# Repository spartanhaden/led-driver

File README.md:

# LED driver

This repo contains code for a [Particle Photon](https://docs.particle.io/quickstart/photon/) used to control a strip of 12V RGB LEDs connected to a custom designed a PCB. The brd and sch files are also included.

## Schematic

## Board

## Breadboard

## PCB

## Assembled PCB

## Assembled unit

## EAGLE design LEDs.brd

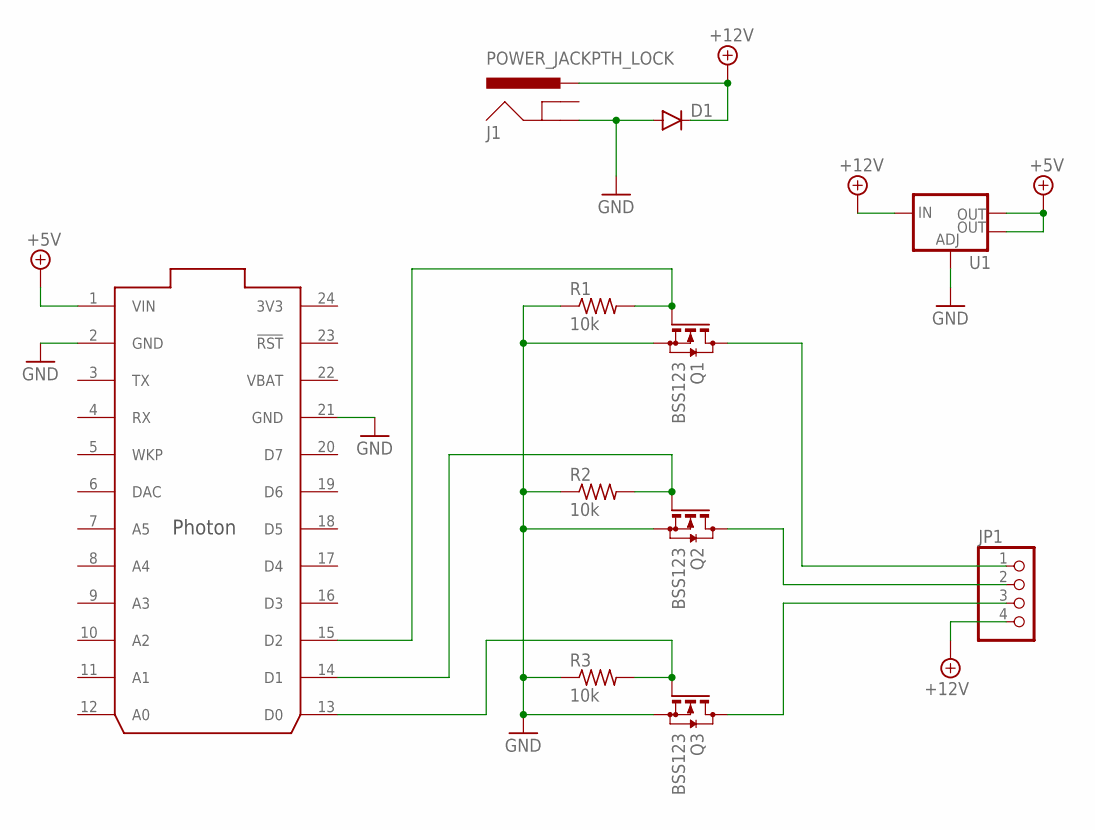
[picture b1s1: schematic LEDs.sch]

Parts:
D1: DIODESMA; SMA-DIODE
J1: POWER_JACKPTH_LOCK; POWER_JACK_PTH_LOCK
JP1: PINHD-1X4/90; 1X04/90
Q1, Q2, Q3: BSS123; SOT23
R1, R2, R3: 10k; M0805
U1: V_REG_LM1117SOT223; SOT223
U$1: PHOTON_WITH_HEADERS; PHOTON

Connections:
3V3: U$1.24 (3V3)
+5V: U1.2 (OUT), U1.4 (OUT), U$1.1 (VIN)
+12V: D1.C, J1.PWR, JP1.4, U1.3 (IN)
GND: D1.A, J1.GND, Q1.2 (S), Q2.2 (S), Q3.2 (S), R1.1, R2.1, R3.1, U1.1 (ADJ), U$1.2 (GND), U$1.21 (GND)
unnamed: Q1.1 (G), R1.2, U$1.15 (D2)
unnamed: Q2.1 (G), R2.2, U$1.14 (D1)
unnamed: Q3.1 (G), R3.2, U$1.13 (D0)
unnamed: JP1.3, Q3.3 (D)
unnamed: JP1.2, Q2.3 (D)
unnamed: JP1.1, Q1.3 (D)
VBAT: U$1.22 (VBAT)

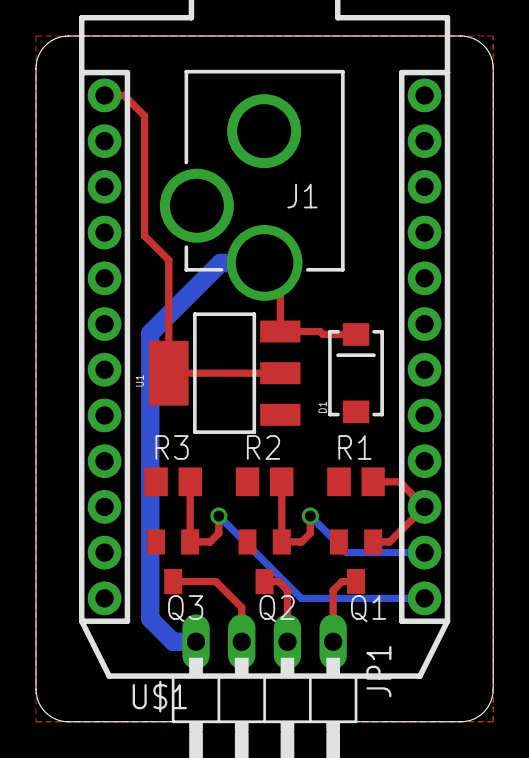
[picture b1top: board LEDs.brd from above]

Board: 2 copper layers, 25.4 x 38.1 mm, 11 parts (0 on the bottom side), 9 nets.

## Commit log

2016-02-16 Initial commit.
2016-03-01 Created color function, added gamma correction, and switched pins
2016-03-18 Added fading on and off.
2016-03-23 Made it turn on before connecting to the internet.
2016-03-23 Changed intensity to brightness for clarity.
2016-03-23 Added code to keep the system time updated.
2016-03-23 Fixes, Polling, and functions.
    Moved LEDs to separate function, fixed naming bug, added checking of
    cloud connection for messages.
2016-03-23 Return final state of LEDs
2016-03-24 Changed threshold, and dimmed onboard LED when disabled.
2016-03-24 Added script to turn lights on/off and gave photon more time to process networking stuff.
2016-04-05 Switched to state based system
    State 2 is only available between 1 AM and 7 AM. It is a dimmed mode
    for pleasant reading before bedtime.
2016-04-06 Updated values.
2016-04-07 Added icon and time zone offset.
2016-04-12 Improved icon quality.
2017-03-30 Rewrote code with support for more input values.
    I completely rewrote the code with support setting brightness level
    remotely. Also updated Readme a little bit.
2017-03-30 Added link to Particle Photon
2017-03-30 Removed extra dash
2021-08-06 Removes capitalization
2021-08-06 Removes exif
2021-08-06 Moves icons to folder
2021-08-06 Fixes incorrect voltage
2021-08-06 Adds images
2021-08-06 Updates formatting
2021-08-06 Updates particle link
2021-08-06 Updates readme title
2021-08-06 Adds OSH Park link
2021-08-06 Updates readme description
2021-08-06 Fixes particle photon link
2021-08-06 Adds more images
2021-08-06 Adds PCB files

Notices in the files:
parts and their libraries:
SparkFun-PowerIC: Licensing: Creative Commons ShareAlike 4.0 International - https://creativecommons.org/licenses/by-sa/4.0
